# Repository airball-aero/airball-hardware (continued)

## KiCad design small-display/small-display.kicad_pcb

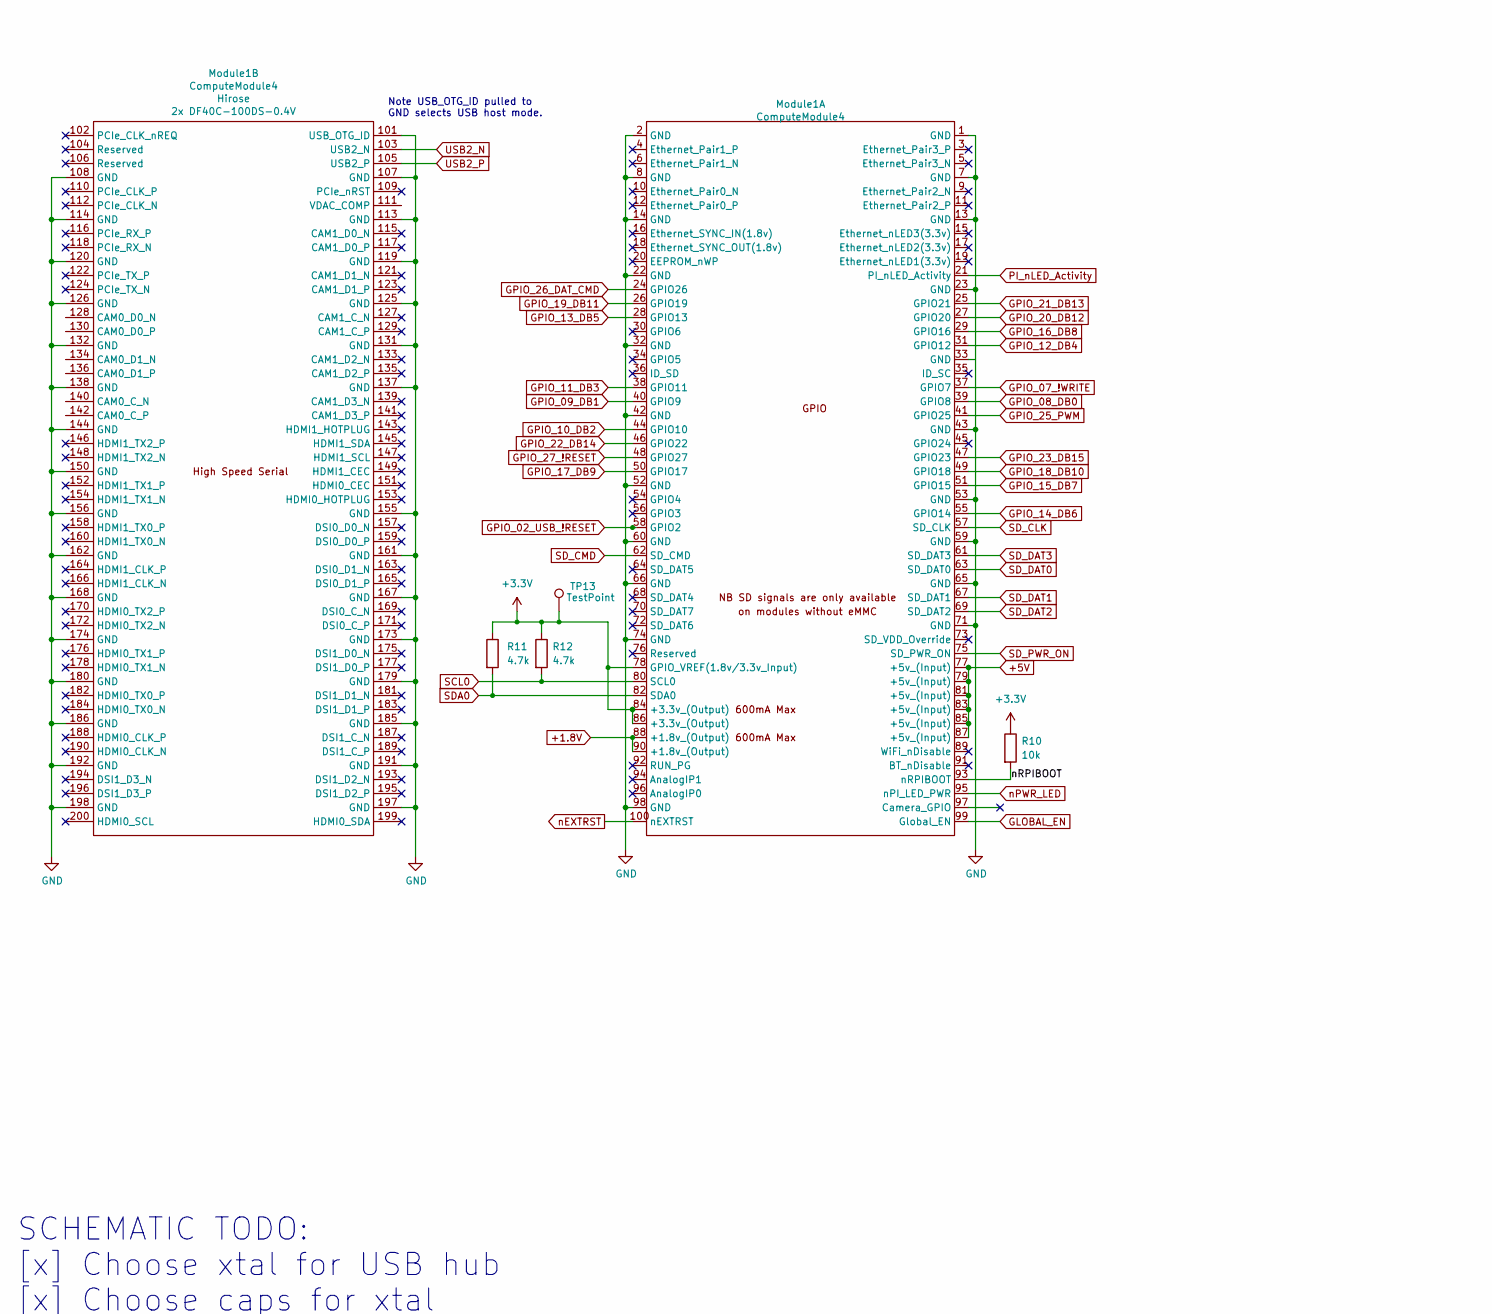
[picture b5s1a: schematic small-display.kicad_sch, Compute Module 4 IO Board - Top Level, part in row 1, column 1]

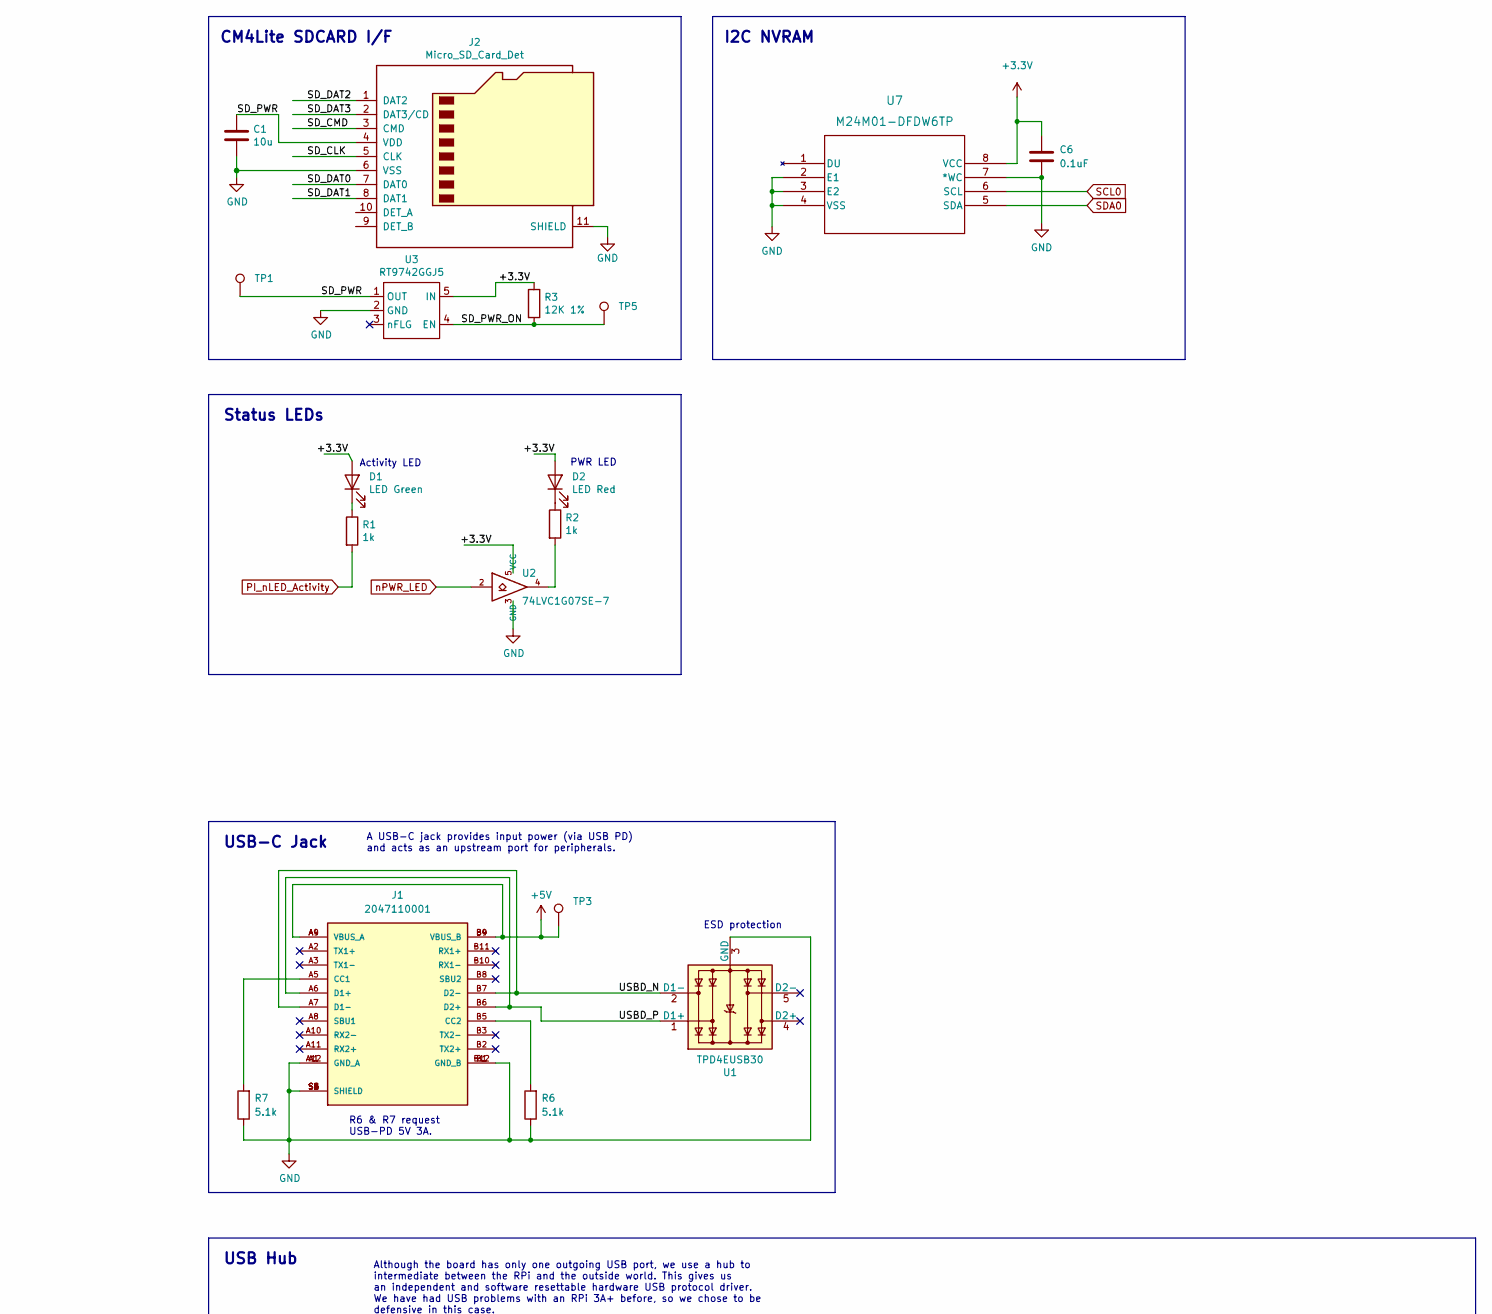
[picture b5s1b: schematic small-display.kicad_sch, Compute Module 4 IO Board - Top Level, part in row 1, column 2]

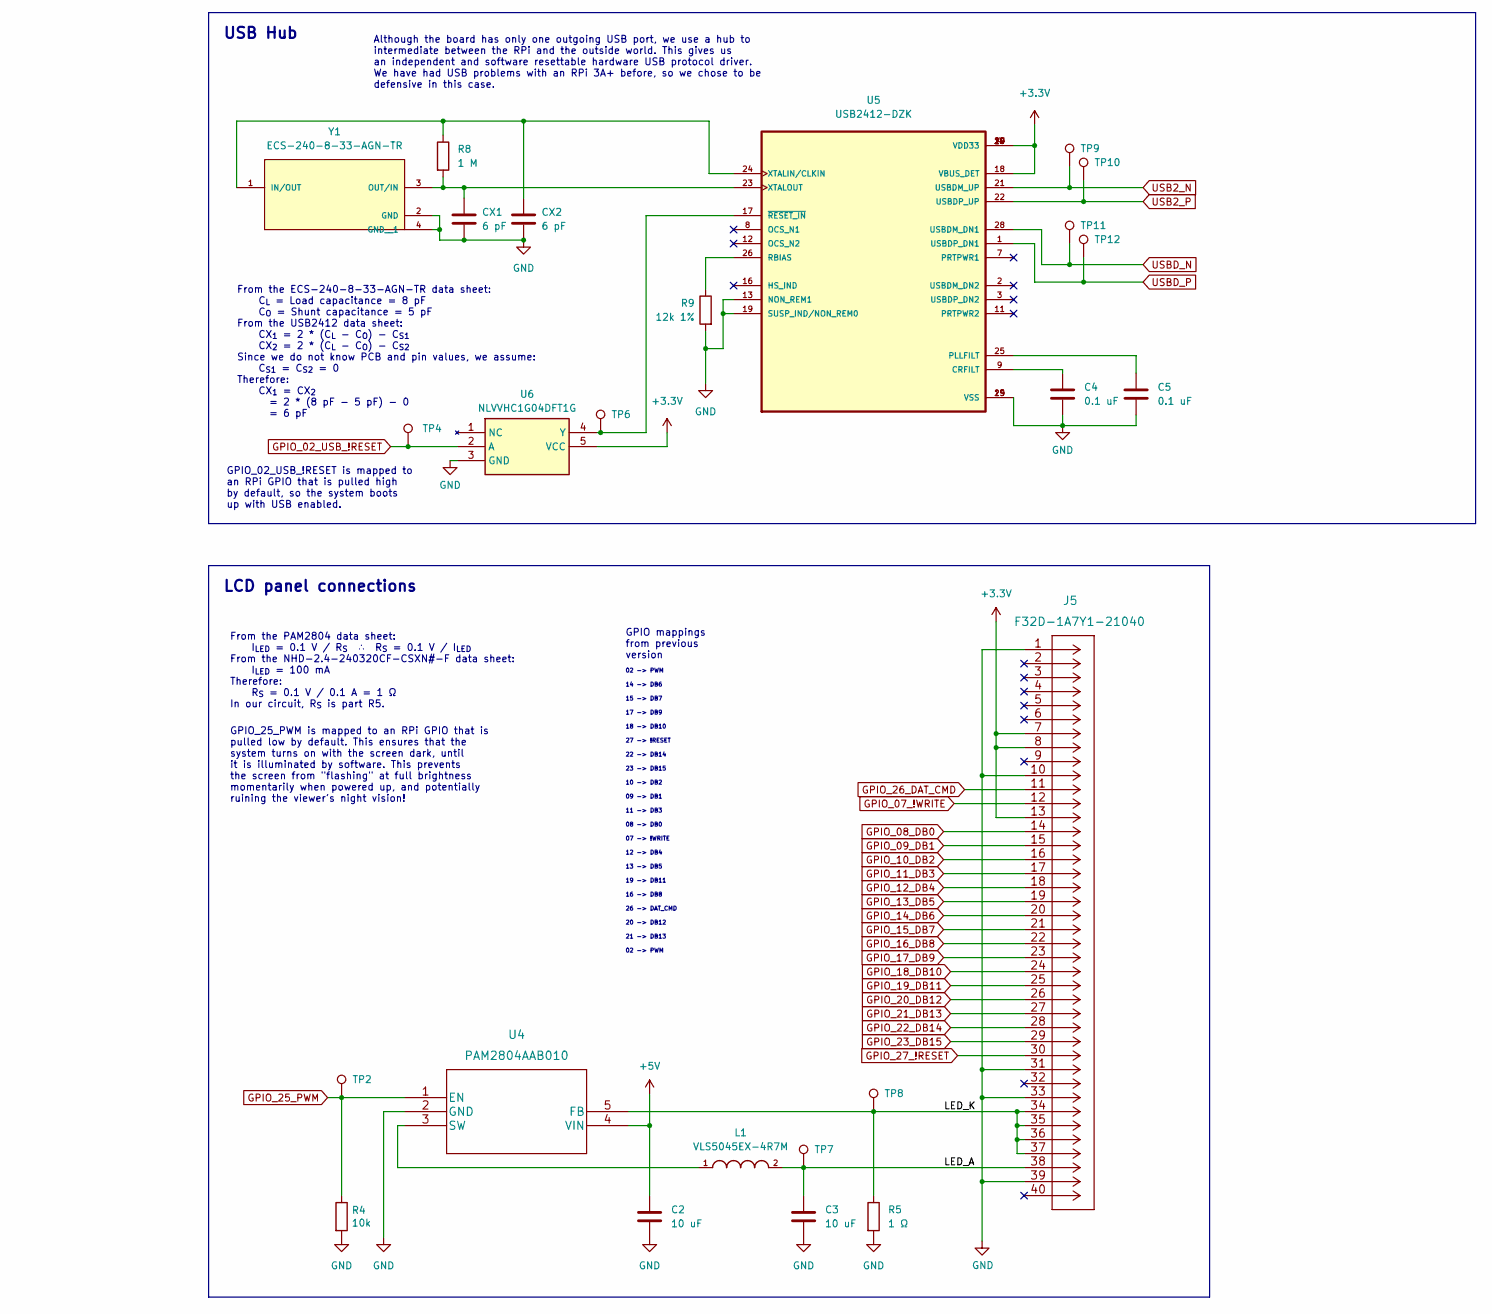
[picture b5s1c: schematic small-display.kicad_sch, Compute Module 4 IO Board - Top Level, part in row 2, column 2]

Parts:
C1: 10u; C_0805_2012Metric; Part Description 10uF 10% 10V Ceramic Capacitor X7R 0805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
C2, C3: 10 uF; C_0603_1608Metric
C4, C5: 0.1 uF; C_0603_1608Metric
C6: 0.1uF; C_0603_1608Metric
CX1, CX2: 6 pF; C_0603_1608Metric
D1: LED Green; LED_0603_1608Metric; Part Description Green 572nm LED Indication - Discrete 2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
D2: LED Red; LED_0603_1608Metric; Part Description Red 620nm LED Indication - Discrete 2.2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
J1: 2047110001; MOLEX_2047110001; PARTREV A3
J2: Micro_SD_Card_Det; SDCARD_MOLEX_503398-1892; Part Description 9 (8 + 1) Position Card Connector micro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
J5: F32D-1A7Y1-21040
L1: VLS5045EX-4R7M; IND_VLS5045EX-4R7M; MPN VLS5045EX-4R7M
Module1: ComputeModule4; Raspberry-Pi-4-Compute-Module; Part Description 100 Position Connector Receptacle, Cent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
R1, R2: 1k; R_0402_1005Metric; Part Description Resistor 1K M1005 1% 63mW
R3: 12K 1%; R_0402_1005Metric; Part Description Resistor 12K M1005 1% 63mW
R4, R10: 10k; R_0402_1005Metric
R5: 1 Ω; R_0402_1005Metric
R6, R7: 5.1k; R_0402_1005Metric
R8: 1 M; R_0402_1005Metric
R9: 12k 1%; R_0402_1005Metric
R11, R12: 4.7k; R_0603_1608Metric
TP1, TP2, TP3, TP4, TP5, TP6, TP7, TP8, TP9, TP10, TP11, TP12, TP13: TestPoint; TestPoint_Pad_D1.0mm
U1: TPD4EUSB30; USON-10_2.5x1.0mm_P0.5mm; Part Description Quad TVS diode for high speed signals (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
U2: 74LVC1G07SE-7; SOT-353_SC-70-5; Part Description Buffer, Non-Inverting 1 Element 1 Bit p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
U3: RT9742GGJ5; SOT-23-5; Part Description Power Switch/Driver 1:1 N-Channel 1A TS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
U4: PAM2804AAB010
U5: USB2412-DZK; QFN50P500X500X100-29N; DIGI-KEY_PART_NUMBER 638-1114-ND
U6: NLVVHC1G04DFT1G; SOT65P210X110-5N; Mouser Part Number 863-NLVVHC1G04DFT1G
U7: M24M01-DFDW6TP; TSSOP_FDW6TP_STM
Y1: ECS-240-8-33-AGN-TR; XTAL_ECS-240-8-33-AGN-TR

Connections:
+1.8V: Module1.88 (+1.8v_(Output)), Module1.90 (+1.8v_(Output))
+3.3V: C6.1, D1.2 (A), D2.2 (A), J5.7, J5.8, J5.13, Module1.78 (GPIO_VREF(1.8v/3.3v_Input)), Module1.84 (+3.3v_(Output)), Module1.86 (+3.3v_(Output)), R3.1, R10.1, R11.1, R12.1, TP13.1, U2.5 (VCC), U3.5 (IN), U5.4 (VDD33), U5.10 (VDD33), U5.14 (VDD33), U5.18 (VBUS_DET), U5.20 (VDD33), U5.27 (VDD33), U6.5 (VCC), U7.8 (VCC)
+5V: C2.1, J1.A4 (VBUS_A), J1.A9 (VBUS_A), J1.B4 (VBUS_B), J1.B9 (VBUS_B), Module1.77 (+5v_(Input)), Module1.79 (+5v_(Input)), Module1.81 (+5v_(Input)), Module1.83 (+5v_(Input)), Module1.85 (+5v_(Input)), Module1.87 (+5v_(Input)), TP3.1, U4.4 (VIN)
/LED_A: C3.1, J5.38, L1.2, TP7.1
/LED_K: J5.34, J5.35, J5.36, J5.37, R5.1, TP8.1, U4.5 (FB)
/SD_PWR: C1.1, J2.4 (VDD), TP1.1, U3.1 (OUT)
/nRPIBOOT: Module1.93 (nRPIBOOT), R10.2
GLOBAL_EN: Module1.99 (Global_EN)
GND: C1.2, C2.2, C3.2, C4.2, C5.2, C6.2, CX1.2, CX2.2, J1.A1 (GND_A), J1.A12 (GND_A), J1.B1 (GND_B), J1.B12 (GND_B), J1.S1 (SHIELD), J1.S2 (SHIELD), J1.S3 (SHIELD), J1.S4 (SHIELD), J1.S5 (SHIELD), J1.S6 (SHIELD), J2.6 (VSS), J2.11 (SHIELD), J5.1, J5.10, J5.31, J5.33, J5.39, Module1.1 (GND), Module1.2 (GND), Module1.7 (GND), Module1.8 (GND), Module1.13 (GND), Module1.14 (GND), Module1.22 (GND), Module1.23 (GND), Module1.32 (GND), Module1.42 (GND), Module1.43 (GND), Module1.52 (GND), Module1.53 (GND), Module1.59 (GND), Module1.60 (GND), Module1.65 (GND), Module1.66 (GND), Module1.71 (GND), Module1.74 (GND), Module1.98 (GND), Module1.101 (USB_OTG_ID), Module1.107 (GND), Module1.108 (GND), Module1.113 (GND), Module1.114 (GND), Module1.119 (GND), Module1.120 (GND), Module1.125 (GND), Module1.126 (GND), Module1.131 (GND), Module1.132 (GND), Module1.137 (GND), Module1.138 (GND), Module1.144 (GND), Module1.150 (GND), Module1.155 (GND), Module1.156 (GND), Module1.161 (GND), Module1.162 (GND), Module1.167 (GND), Module1.168 (GND), Module1.173 (GND), Module1.174 (GND), Module1.179 (GND), Module1.180 (GND), Module1.185 (GND), Module1.186 (GND), Module1.191 (GND), Module1.192 (GND), Module1.197 (GND), Module1.198 (GND), R4.2, R5.2, R6.1, R7.1, R9.2, U1.3 (GND), U1.8 (GND), U2.3 (GND), U3.2 (GND), U4.2 (GND), U5.13 (NON_REM1), U5.15 (VSS), U5.19 (SUSP_IND/NON_REM0), U5.29 (VSS), U6.3 (GND), U7.2 (E1), U7.3 (E2), U7.4 (VSS), U7.7 (*WC), Y1.2 (GND), Y1.4 (GND__1)
GPIO_02_USB_!RESET: Module1.58 (GPIO2), TP4.1, U6.2 (A)
GPIO_07_!WRITE: J5.12, Module1.37 (GPIO7)
GPIO_08_DB0: J5.14, Module1.39 (GPIO8)
GPIO_09_DB1: J5.15, Module1.40 (GPIO9)
GPIO_10_DB2: J5.16, Module1.44 (GPIO10)
GPIO_11_DB3: J5.17, Module1.38 (GPIO11)
GPIO_12_DB4: J5.18, Module1.31 (GPIO12)
GPIO_13_DB5: J5.19, Module1.28 (GPIO13)
GPIO_14_DB6: J5.20, Module1.55 (GPIO14)
GPIO_15_DB7: J5.21, Module1.51 (GPIO15)
GPIO_16_DB8: J5.22, Module1.29 (GPIO16)
GPIO_17_DB9: J5.23, Module1.50 (GPIO17)
GPIO_18_DB10: J5.24, Module1.49 (GPIO18)
GPIO_19_DB11: J5.25, Module1.26 (GPIO19)
GPIO_20_DB12: J5.26, Module1.27 (GPIO20)
GPIO_21_DB13: J5.27, Module1.25 (GPIO21)
GPIO_22_DB14: J5.28, Module1.46 (GPIO22)
GPIO_23_DB15: J5.29, Module1.47 (GPIO23)
GPIO_25_PWM: Module1.41 (GPIO25), R4.1, TP2.1, U4.1 (EN)
GPIO_26_DAT_CMD: J5.11, Module1.24 (GPIO26)
GPIO_27_!RESET: J5.30, Module1.48 (GPIO27)
unnamed: C4.1, U5.9 (CRFILT)
unnamed: C5.1, U5.25 (PLLFILT)
unnamed: CX1.1, R8.2, U5.23 (XTALOUT), Y1.3 (OUT/IN)
unnamed: CX2.1, R8.1, U5.24 (XTALIN/CLKIN), Y1.1 (IN/OUT)
unnamed: D1.1 (K), R1.1
unnamed: D2.1 (K), R2.1
unnamed: J1.A5 (CC1), R7.2
unnamed: J1.B5 (CC2), R6.2
unnamed: L1.1, U4.3 (SW)
unnamed: R2.2, U2.4
unnamed: R9.1, U5.26 (RBIAS)
unnamed: TP6.1, U5.17 (~RESET_IN), U6.4 (Y)
PI_nLED_Activity: Module1.21 (PI_nLED_Activity), R1.2
SCL0: Module1.80 (SCL0), R12.2, U7.6 (SCL)
SDA0: Module1.82 (SDA0), R11.2, U7.5 (SDA)
SD_CLK: J2.5 (CLK), Module1.57 (SD_CLK)
SD_CMD: J2.3 (CMD), Module1.62 (SD_CMD)
SD_DAT0: J2.7 (DAT0), Module1.63 (SD_DAT0)
SD_DAT1: J2.8 (DAT1), Module1.67 (SD_DAT1)
SD_DAT2: J2.1 (DAT2), Module1.69 (SD_DAT2)
SD_DAT3: J2.2 (DAT3/CD), Module1.61 (SD_DAT3)
SD_PWR_ON: Module1.75 (SD_PWR_ON), R3.2, TP5.1, U3.4 (EN)
USB2_N: Module1.103 (USB2_N), TP9.1, U5.21 (USBDM_UP)
USB2_P: Module1.105 (USB2_P), TP10.1, U5.22 (USBDP_UP)
USBD_N: J1.A7 (D1-), J1.B7 (D2-), TP11.1, U1.2 (D1-), U1.9, U5.28 (USBDM_DN1)
USBD_P: J1.A6 (D1+), J1.B6 (D2+), TP12.1, U1.1 (D1+), U1.10, U5.1 (USBDP_DN1)
nEXTRST: Module1.100 (nEXTRST)
nPWR_LED: Module1.95 (nPI_LED_PWR), U2.2

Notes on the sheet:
13 -> DB5
From the ECS-240-8-33-AGN-TR data sheet: C_{L} = Load capacitance = 8 pF C_{O} = Shunt capacitance = 5 pF From the USB2412 data sheet: CX_{1} = 2 * (C_{L} - C_{O}) - C_{S1} CX_{2} = 2 * (C_{L} - C_{O}) - C_{S2} Since we do not know PCB and pin values, we assume: C_{S1} = C_{S2} = 0 Therefore: CX_{1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
09 -> DB1
ESD protection
USB-C Jack
I2C NVRAM
A USB-C jack provides input power (via USB PD) and acts as an upstream port for peripherals.
Activity LED
GPIO_02_USB_!RESET is mapped to an RPi GPIO that is pulled high by default, so the system boots up with USB enabled.
17 -> DB9
15 -> DB7
Status LEDs
18 -> DB10
PWR LED
GPIO mappings from previous version
16 -> DB8
SCHEMATIC TODO: [x] Choose xtal for USB hub [x] Choose caps for xtal [x] Wire up USB hub (both ends) [x] Decide on RESET line for USB hub [x] Wire up power connections [x] Figure out GPIO mappings for display [x] Choose a GPIO for USB_RESET [x] Wire up display connections [ ] Review all RPi pinouts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
USB Hub
14 -> DB6
10 -> DB2
23 -> DB15
LCD panel connections
22 -> DB14
From the PAM2804 data sheet: I_{LED} = 0.1 V / R_{S} ∴ R_{S} = 0.1 V / I_{LED} From the NHD-2.4-240320CF-CSXN#-F data sheet: I_{LED} = 100 mA Therefore: R_{S} = 0.1 V / 0.1 A = 1 Ω In our circuit, R_{S} is part R5.
19 -> DB11
26 -> DAT_CMD
Although the board has only one outgoing USB port, we use a hub to intermediate between the RPi and the outside world. This gives us an independent and software resettable hardware USB protocol driver. We have had USB problems with an RPi 3A+ before, so we chose to be defensive in this case.
02 -> PWM
20 -> DB12
08 -> DB0
GPIO_25_PWM is mapped to an RPi GPIO that is pulled low by default. This ensures that the system turns on with the screen dark, until it is illuminated by software. This prevents the screen from "flashing" at full brightness momentarily when powered up, and potentially ruining the viewer's night vi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
Note USB_OTG_ID pulled to GND selects USB host mode.
CM4Lite SDCARD I/F
12 -> DB4
27 -> !RESET
21 -> DB13
11 -> DB3
07 -> !WRITE
R6 & R7 request USB-PD 5V 3A.

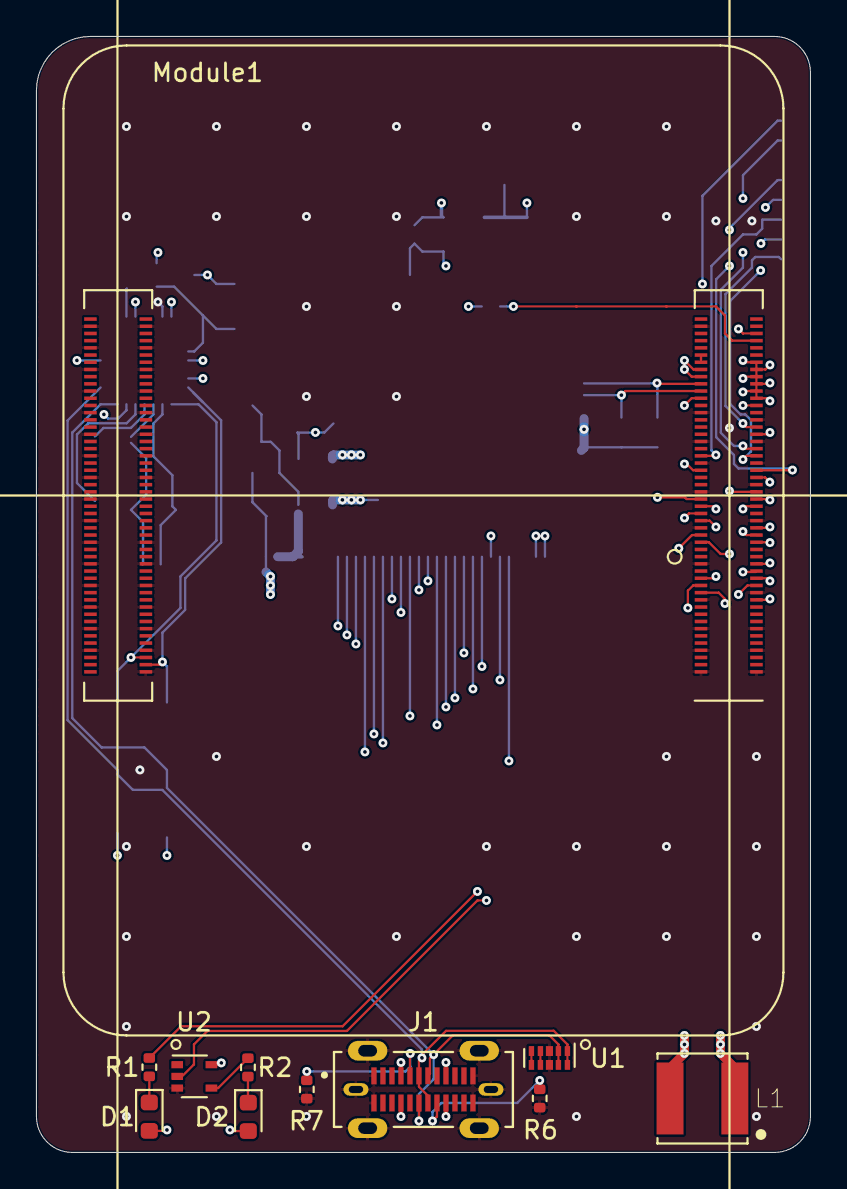
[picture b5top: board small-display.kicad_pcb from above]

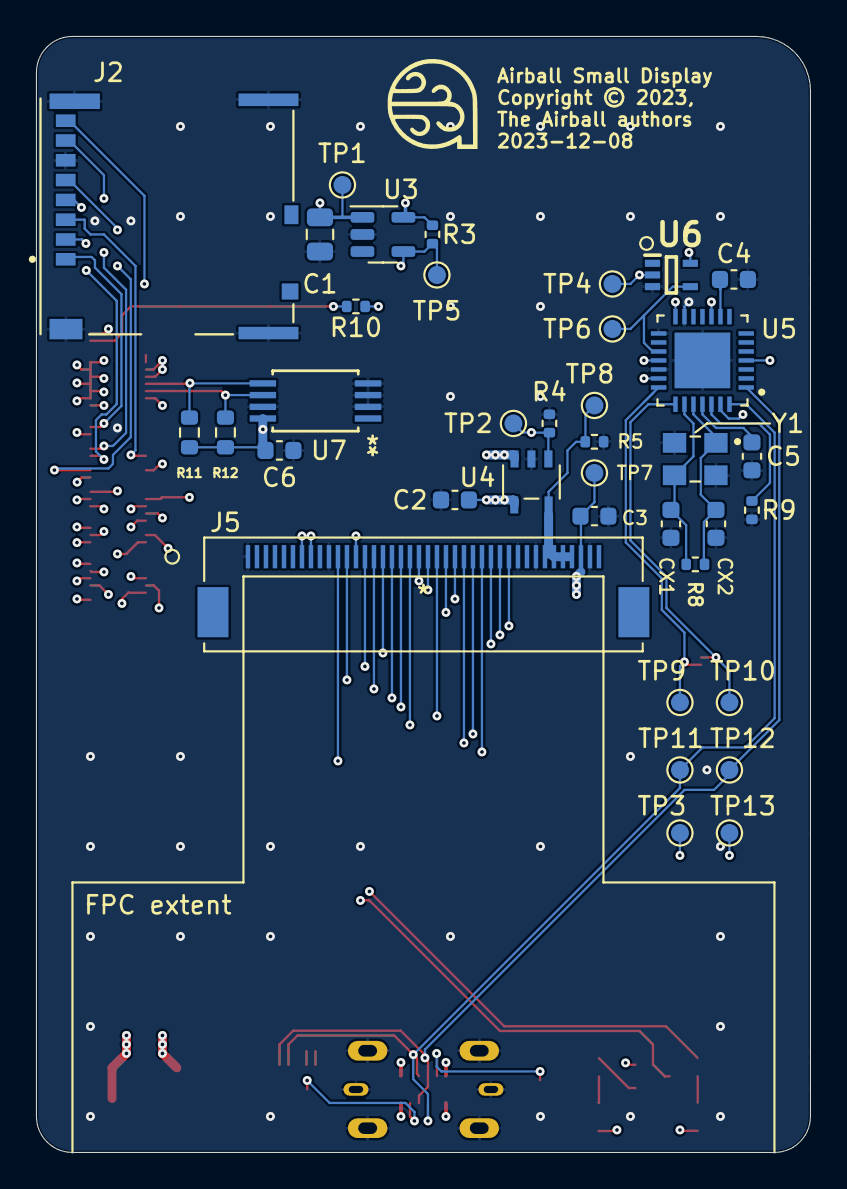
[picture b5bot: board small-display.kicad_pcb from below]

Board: 4 copper layers, 43.0 x 62.0 mm, 48 parts (37 on the bottom side), 56 nets.

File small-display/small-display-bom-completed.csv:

Id,Designator,Package,Quantity,Designation,Supplier and ref
1,"R1,R2",R_0402_1005Metric,2,1k,Common part
2,"R6,R7",R_0402_1005Metric,2,5.1k,Common part
3,J1,MOLEX_2047110001,1,2047110001,https://www.digikey.com/en/products/detail/molex/2047110001/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
4,U2,SOT-353_SC-70-5,1,74LVC1G07SE-7,https://www.digikey.com/en/products/detail/diodes-incorporat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
5,U1,USON-10_2.5x1.0mm_P0.5mm,1,TPD4EUSB30,https://www.digikey.com/en/products/detail/texas-instruments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
6,D2,LED_0603_1608Metric,1,LED Red,Common part
7,L1,IND_VLS5045EX-4R7M,1,VLS5045EX-4R7M,https://www.digikey.com/en/products/detail/tdk-corporation/V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
8,D1,LED_0603_1608Metric,1,LED Green,Common part
9,Module1,Raspberry-Pi-4-Compute-Module,2,DF40C-100DS-0.4V(51),https://www.digikey.com/en/products/detail/hirose-electric-c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
10,"TP4,TP1,TP5,TP10,TP11,TP8,TP2,TP7,TP13,TP12,TP6,TP3,TP9",TestPoint_Pad_D1.0mm,13,TestPoint,DNP
11,"R4,R10",R_0402_1005Metric,2,10k,Common part
12,"C4,C5",C_0603_1608Metric,2,0.1 uF,Common part
13,U6,SOT65P210X110-5N,1,NLVVHC1G04DFT1G,https://www.digikey.com/en/products/detail/onsemi/NLVVHC1G04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
14,"C2,C3",C_0603_1608Metric,2,10 uF,Common part
15,"CX2,CX1",C_0603_1608Metric,2,6 pF,Common part
16,U5,QFN50P500X500X100-29N,1,USB2412-DZK,https://www.digikey.com/en/products/detail/microchip-technol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
17,R8,R_0402_1005Metric,1,1 M,Common part
18,U4,PAM2804AAB010,1,PAM2804AAB010,https://www.digikey.com/en/products/detail/diodes-incorporat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
19,U3,SOT-23-5,1,RT9742GGJ5,https://www.digikey.com/en/products/detail/richtek-usa-inc/R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
20,R3,R_0402_1005Metric,1,12K 1%,Common part
21,C1,C_0805_2012Metric,1,10u,Common part
22,J2,SDCARD_MOLEX_503398-1892,1,Micro_SD_Card_Det,https://www.digikey.com/en/products/detail/molex/5033981892/4555393
23,Y1,XTAL_ECS-240-8-33-AGN-TR,1,ECS-240-8-33-AGN-TR,https://www.digikey.com/en/products/detail/ecs-inc/ECS-240-8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
24,R9,R_0402_1005Metric,1,12k 1%,Common part
25,C6,C_0603_1608Metric,1,0.1uF,Common part
26,U7,TSSOP_FDW6TP_STM,1,M24M01-DFDW6TP,https://www.digikey.com/en/products/detail/stmicroelectronic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
27,R5,R_0402_1005Metric,1,1 Ω,Common part
28,J5,F32D-1A7Y1-21040,1,F32D-1A7Y1-21040,https://www.digikey.com/en/products/detail/amphenol-cs-fci/F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
29,"R12,R11",R_0603_1608Metric,2,4.7k,Common part

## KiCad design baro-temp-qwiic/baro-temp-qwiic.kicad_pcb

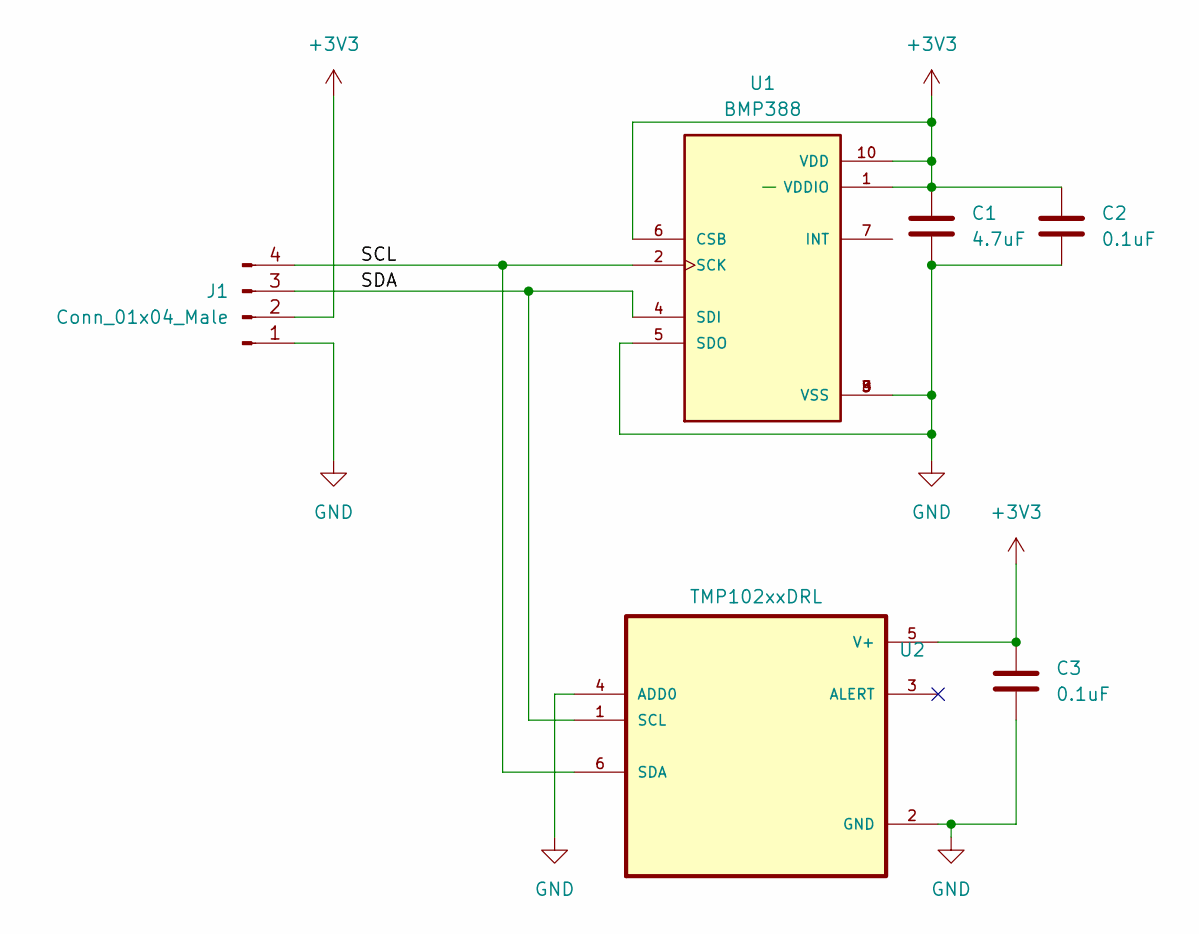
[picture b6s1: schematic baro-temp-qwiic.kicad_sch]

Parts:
C1: 4.7uF; C_0603_1608Metric
C2, C3: 0.1uF; C_0603_1608Metric
J1: Conn_01x04_Male; JST_SH_BM04B-SRSS-TB_1x04-1MP_P1.00mm_Vertical
U1: BMP388; PARTREV 1.1
U2: TMP102xxDRL; TMP102 - SOT50P160X60-6N

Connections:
+3V3: C1.1, C2.1, C3.1, J1.2, U1.1 (VDDIO), U1.6 (CSB), U1.10 (VDD), U2.5 (V+)
/SCL: J1.4, U1.2 (SCK), U2.6 (SDA)
/SDA: J1.3, U1.4 (SDI), U2.1 (SCL)
GND: C1.2, C2.2, C3.2, J1.1, U1.3 (VSS), U1.5 (SDO), U1.8 (VSS), U1.9 (VSS), U2.2 (GND), U2.4 (ADD0)

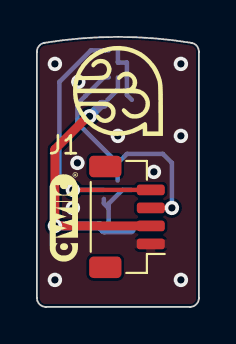
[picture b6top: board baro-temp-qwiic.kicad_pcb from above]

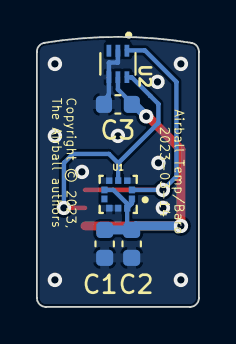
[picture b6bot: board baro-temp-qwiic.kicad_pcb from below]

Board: 2 copper layers, 9.0 x 15.0 mm, 6 parts (5 on the bottom side), 4 nets.

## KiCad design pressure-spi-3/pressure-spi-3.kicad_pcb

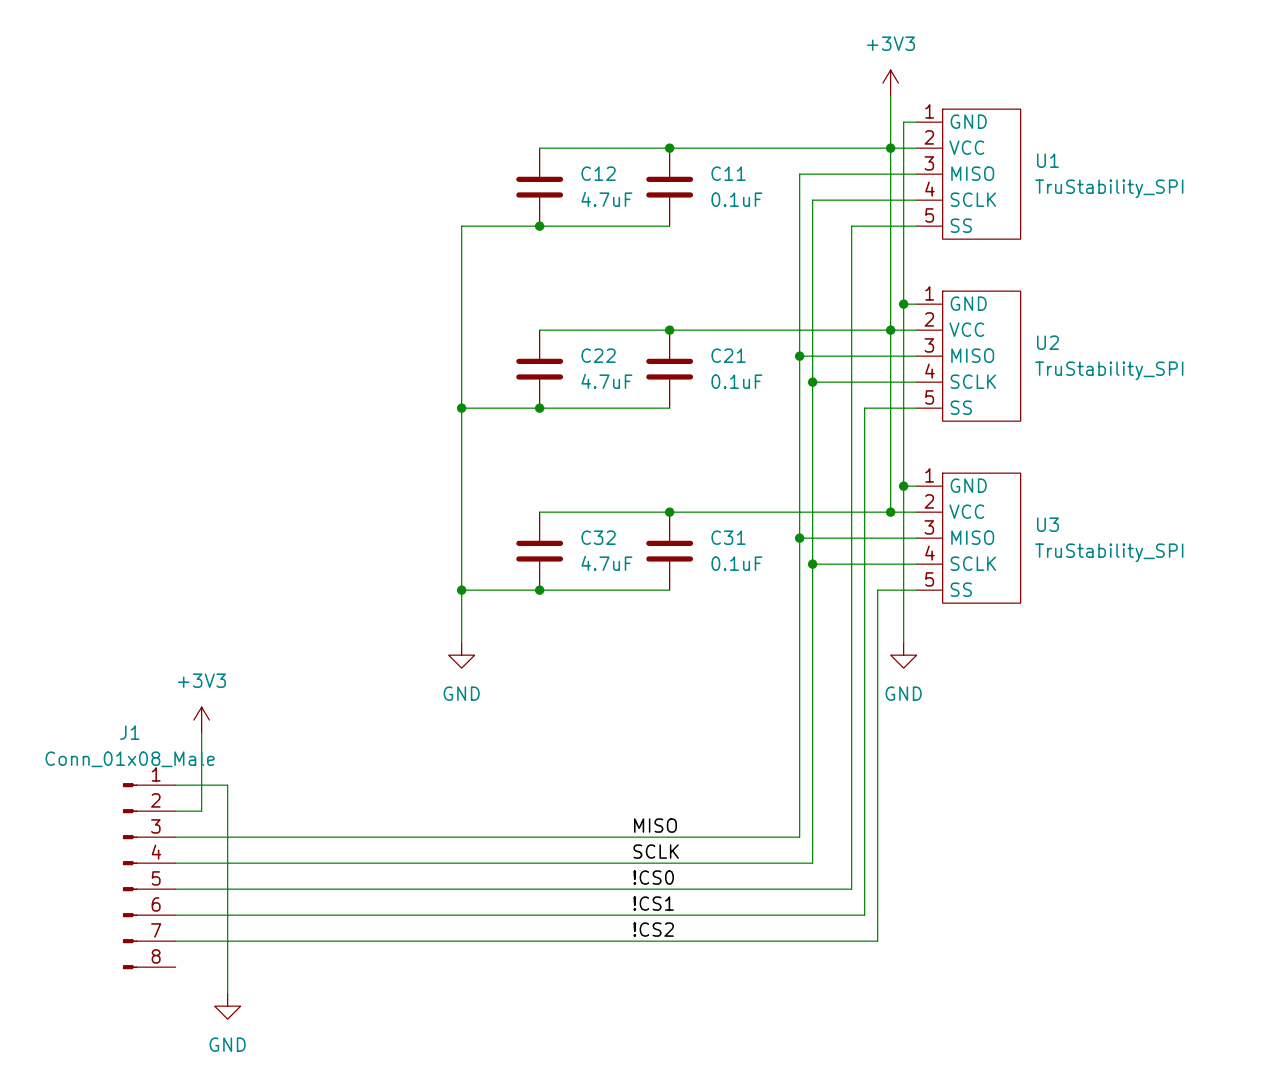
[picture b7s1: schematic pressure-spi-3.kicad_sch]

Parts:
C11, C21, C31: 0.1uF; C_0603_1608Metric
C12, C22, C32: 4.7uF; C_0603_1608Metric
J1: Conn_01x08_Male; JST_SH_BM08B-SRSS-TB_1x08-1MP_P1.00mm_Vertical
U1, U2, U3: TruStability_SPI; TruStability SMT

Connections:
+3V3: C11.1, C12.1, C21.1, C22.1, C31.1, C32.1, J1.2, U1.2 (VCC), U2.2 (VCC), U3.2 (VCC)
/!CS0: J1.5, U1.5 (SS)
/!CS1: J1.6, U2.5 (SS)
/!CS2: J1.7, U3.5 (SS)
/MISO: J1.3, U1.3 (MISO), U2.3 (MISO), U3.3 (MISO)
/SCLK: J1.4, U1.4 (SCLK), U2.4 (SCLK), U3.4 (SCLK)
GND: C11.2, C12.2, C21.2, C22.2, C31.2, C32.2, J1.1, J1.MP, U1.1 (GND), U2.1 (GND), U3.1 (GND)

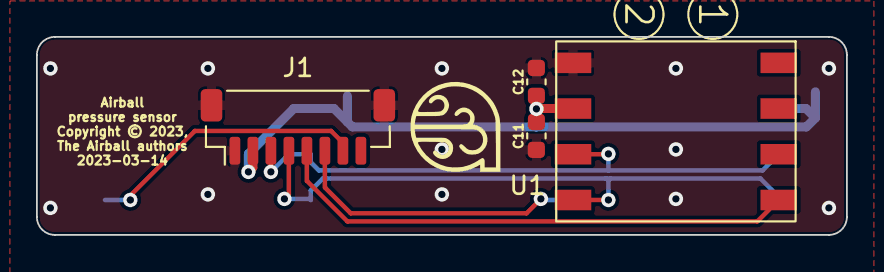
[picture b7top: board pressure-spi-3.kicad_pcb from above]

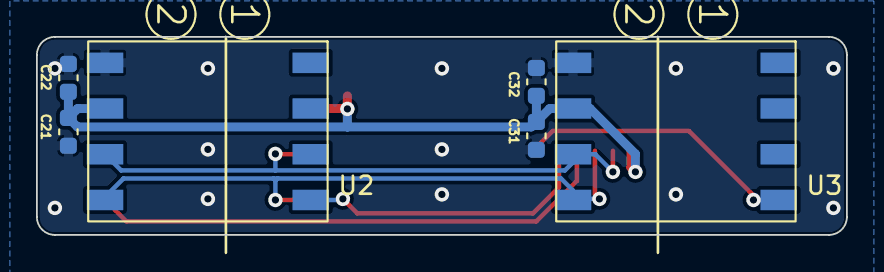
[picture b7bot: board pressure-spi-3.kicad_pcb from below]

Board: 2 copper layers, 45.0 x 11.0 mm, 10 parts (6 on the bottom side), 7 nets.

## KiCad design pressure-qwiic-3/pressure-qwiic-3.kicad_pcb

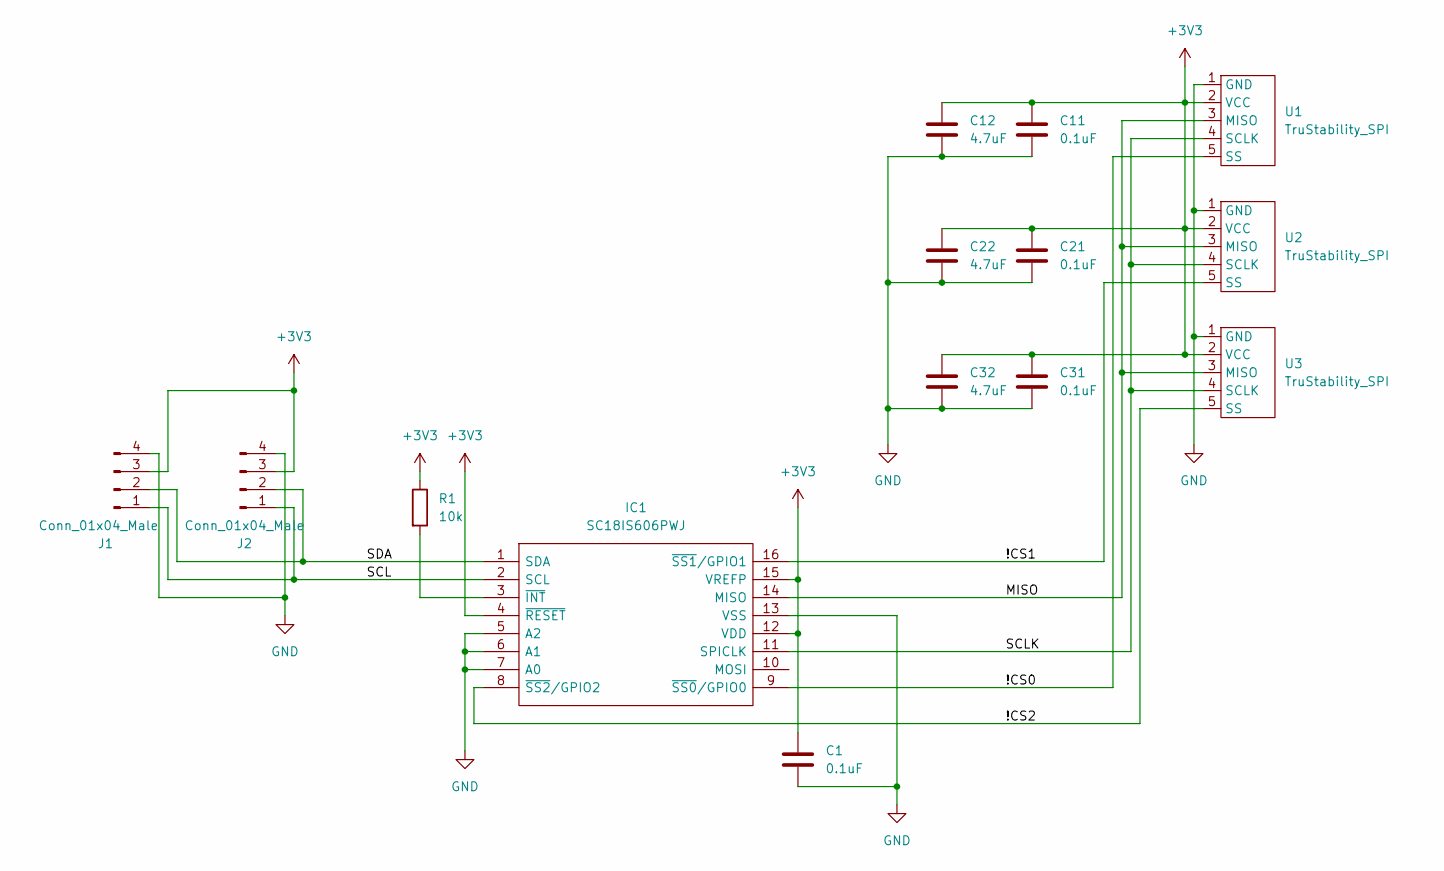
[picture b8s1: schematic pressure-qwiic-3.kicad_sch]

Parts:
C1, C11, C21, C31: 0.1uF; C_0603_1608Metric
C12, C22, C32: 4.7uF; C_0603_1608Metric
IC1: SC18IS606PWJ; SOP65P640X110-16N; Manufacturer_Part_Number SC18IS606PWJ
J1, J2: Conn_01x04_Male; JST_SH_BM04B-SRSS-TB_1x04-1MP_P1.00mm_Vertical
R1: 10k; R_0603_1608Metric
U1, U2, U3: TruStability_SPI; TruStability SMT

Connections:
+3V3: C1.1, C11.1, C12.1, C21.1, C22.1, C31.1, C32.1, IC1.4 (~RESET), IC1.12 (VDD), IC1.15 (VREFP), J1.3, J2.3, R1.1, U1.2 (VCC), U2.2 (VCC), U3.2 (VCC)
/!CS0: IC1.9 (~SS0/GPIO0), U1.5 (SS)
/!CS1: IC1.16 (~SS1/GPIO1), U2.5 (SS)
/!CS2: IC1.8 (~SS2/GPIO2), U3.5 (SS)
/MISO: IC1.14 (MISO), U1.3 (MISO), U2.3 (MISO), U3.3 (MISO)
/SCL: IC1.2 (SCL), J1.1, J2.1
/SCLK: IC1.11 (SPICLK), U1.4 (SCLK), U2.4 (SCLK), U3.4 (SCLK)
/SDA: IC1.1 (SDA), J1.2, J2.2
GND: C1.2, C11.2, C12.2, C21.2, C22.2, C31.2, C32.2, IC1.5 (A2), IC1.6 (A1), IC1.7 (A0), IC1.13 (VSS), J1.4, J2.4, U1.1 (GND), U2.1 (GND), U3.1 (GND)
unnamed: IC1.3 (~INT), R1.2

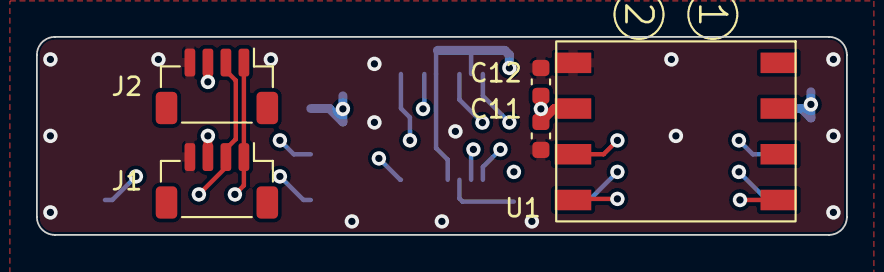
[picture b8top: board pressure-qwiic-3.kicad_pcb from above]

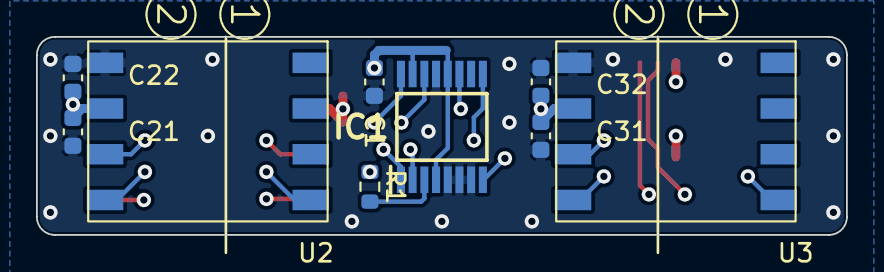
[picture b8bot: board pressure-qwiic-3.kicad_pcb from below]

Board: 4 copper layers, 45.0 x 11.0 mm, 14 parts (9 on the bottom side), 10 nets.

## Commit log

2022-12-10 Ignore KiCad autosave files.
2022-12-10 Daughterboard for Raspberry Pi 3A+ to use NHD high brightness display.
2022-12-10 Updated 3D models and silk screen.
2022-12-10 Minor update to clearances.
2022-12-15 More work on the general board layout and pressure sensor locations.
2022-12-17 Completed a first pass of the routing.
2022-12-18 More routing and silk screen improvements.
2022-12-20 Updated routing and board layout.
2022-12-20 More work on the silk screen.
2023-01-28 Added new library. Starting work on a QWIIC compatible carrier board for 3 Honeywell SPI pressure sensors.
2023-01-28 Ongoing work.
2023-01-28 Fixed QWIIC pinouts. Added QWIIC logo.
2023-03-03 Latest changes.
2023-03-04 Almost complete.
2023-03-04 More changes. Should be ready now.
2023-03-05 Completed pressure-qwiic-3. Completed baro-temp-qwiic. Deleted baro-qwiic.
2023-03-05 Ongoing changes.
2023-03-05 Made board smaller to fit better into probe.
2023-03-07 Moved to 4 layer PCB and shrank the size. Re-routed.
2023-03-09 Added some useful FPC connectors.
2023-03-09 Removed KiCAD auto-backups.
2023-03-10 Re-routed.
2023-03-10 Support files for library entries.
2023-03-11 Moved 8-pin connector for better clearance.
2023-03-12 More components.
2023-03-12 Finished first cut of routing.
2023-03-12 Exported STEP file
2023-03-12 Minor changes.
2023-03-12 Final changes.
2023-03-12 Minor appearance finishing touches.
2023-03-14 Added CANBus 120 ohm termination resistor.
2023-03-15 Finished design & created fab outputs.
2023-03-15 Finished design and produced fab outputs.
2023-03-15 Removed obsolete board.
2023-03-15 Finished design and made fab outputs.
2023-03-15 Updated BOM.
2023-03-16 Added TMP102 symbol with footprint pads sized for enough solder mask clearance.
2023-03-16 Re-spun board for better solder mask clearance.
2023-03-16 Removing spurious lockfile.
2023-07-04 Starting to work on a custom small (2.4" screen) display.
2023-07-04 Continued work on small display PCB.
2023-07-05 More work on small display.
2023-07-07 More routing and design of small display.
2023-07-08 Routing the board.
2023-07-08 More routing of small-display.
2023-07-09 First complete routing done.
2023-07-09 More routing refinements.
2023-07-09 More routing improvements.
2023-07-14 More or less complete except for DRC.
2023-07-14 Tweaking silk screen.
2023-07-15 Finished DRC.
2023-07-15 Updated design outputs.
2023-07-15 Updated zipfile.
2023-07-15 Ran DRC again and updated production outputs.
2023-07-15 Added convenience files for completed BOM and centroids.
2023-07-15 Updated Gerbers after refreshing zones.
2023-07-15 Another run of rebuilding copper pours and running DRC.
2023-07-15 Updated design files.
2023-12-08 Added 4.7k I2C pullup resistors.
2023-12-08 Remove STEP file.
2023-12-08 Added 5V power converter and CANBus chip.
2023-12-09 Changed to new power supply and different CANBus chip.
2023-12-09 Added logo and copyright.
2023-12-09 Fixed symbol.
2023-12-09 Updating fab outputs.
2023-12-09 Added manufacturing data.
2024-02-02 Added Omron tactile switches to library.
2024-02-02 Added stick switch component.
2024-02-02 Use real mounting holes, not just vias.
2024-02-03 Moved mounting holes.
2024-02-04 Made PTT and Trim common separate nets. Finalized layout and generated Gerbers.
2024-02-04 Adding final saved changes.
2024-03-24 Added more symbols.
2024-03-24 Remove "margin" from symbols.
2024-03-24 Fixes to lib.
2024-03-24 Prototype knob for displays.
2025-03-22 Added "RN" (1 port) version of Honeywell sensor.
2025-03-22 New 4-sensor SPI sensor board.
2025-03-23 Moved sensors to +/- 0.512 inches exactly.
2025-03-31 Additions to library.
2025-03-31 Designed and routed board.
